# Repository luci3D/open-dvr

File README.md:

# open-dvr

An open recorder for the BAYCKRC / COOAI "MINI DVR", a small analog FPV DVR board (Goke GK7202V300 SoC + Techpoint TP2850 video decoder). It's built on open-source work from the [OpenIPC](https://openipc.org) project.

- Real 50 fps PAL and 59.94 fps NTSC: every video field is recorded, where the stock firmware repeats each picture twice.
- H.264 in MPEG-TS clips, safe against power cuts, with the board's microphone as an in-sync MP3 track.
- Runs from the SD card through the board's own boot hook. Nothing is flashed, and removing the files brings back the stock firmware.

| Folder | What |
|---|---|
| [`dvr-recorder/`](dvr-recorder/) | The recorder (`dvrrec`): specs, wiring, settings, build steps, credits |
| [`dvr-probe/`](dvr-probe/) | The SD card probe script used to work out the hardware |
| [`imu-probe/`](imu-probe/) | IMU test for the next, Rockchip-based generation (see [`ROADMAP.md`](ROADMAP.md)) |

Quick start: download `open-dvr-0.9.zip` from the [Releases](https://github.com/luci3D/open-dvr/releases) page, extract it into the top folder of the board's SD card, and power on. The zip has its own `README.txt` with the button, the LEDs and every `config.txt` setting. The technical details are in [`dvr-recorder/README.md`](dvr-recorder/README.md).

Where the project goes from here: [`ROADMAP.md`](ROADMAP.md). Stage 1, this board, is done; stage 2 is our own hardware on the Rockchip RV1103.

## Licence

GPL-3.0, see [`LICENSE`](LICENSE). Third-party parts keep their own licences; see [Credits and licences](dvr-recorder/README.md#credits-and-licences).

Not affiliated with OpenIPC or with the board's maker.

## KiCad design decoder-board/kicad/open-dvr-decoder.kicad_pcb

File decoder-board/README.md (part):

# Decoder board (phase 1): the DIY kit board

A small board that turns an analog FPV camera signal (CVBS) into MIPI CSI-2 for a Luckfox Pico, and carries the DVR's microphone. Plugged into a Luckfox Pico Pro/Max with the camera ribbon cable and a few wires, it makes a complete DVR module. It is **our first piece of hardware and the DIY kit board** (decided 2026-11-19): video decoder and mic, on a separate board connected by cable. The IMU stays a separate breakout for later ([roadmap phase 4](../ROADMAP.md#phase-4-imu-breakout)).

Status: **schematic v0.1, PCB placed and routed v0.1, 2026-11-19** ([`kicad/`](kicad/), see [Schematic](#schematic) and [PCB](#pcb)). Next: a review in KiCad, then a JLC order.

| Top | Bottom |
|---|---|
|  |  |

KiCad 3D renders of v0.2 with all parts fitted (U1 and MK1 included, though they are soldered at home).

```
FC video line ──(parallel tap)──► J2/J3 ──► input network ──► TP9950 ──MIPI 2 lanes + I2C──► J1 FPC ──► Luckfox camera connector
FC 5 V ──► J2/J3 ──► reverse-polarity FET ──► 5 V ──► 3.3 V LDO, 1.2 V buck, camera 5 V out (J3), 5 V to Luckfox VSYS (J3)
MEMS mic ──► J3 ──(3 short wires)──► Luckfox codec pads 3/4 + GND
```

## Connectors

| Ref | Type | Pins | Goes to |
|---|---|---|---|
| J1 | FPC 0.5 mm 20-pin, **top contact** (05B20U20P, JLC-assembled) | Luckfox camera pinout, pin n = Luckfox pin n | Luckfox camera connector, stock opposite-side cable |
| J2 | SH 1.0 mm 3-pin (JLC-assembled) | 1 Video, 2 5 V in, 3 GND | The FC: camera video line (parallel tap) and 5 V; same harness as the COOAI DVR |
| J3 | One row of 10 holes, 2.54 mm, along the bottom edge (not assembled) | see below | Wires, or a 10-pin header for a breadboard |

J3, labelled on the silkscreen, left to right:

| Pin | Label | Net | Goes to |
|---|---|---|---|
| 1 | VID | Video in | Same as J2 pin 1 |
| 2 | VG | Video ground sense (VID_REF) | The camera's ground at the tap, on its own wire twisted with VID. Optional: R16 ties it to GND (see [Video input network](#video-input-network)) |
| 3 | 5Vin | 5 V in | Same as J2 pin 2 |
| 4 | GND | GND | |
| 5 | CAM | Camera 5 V out, through the polyfuse | A camera on the bench |
| 6 | GND | GND | |
| 7 | VSYS | 5 V out | Luckfox **VSYS (header pin 39)**: one 5 V feed from the FC powers both boards. VSYS is the Luckfox's 5 V system rail; its USB-C input reaches it through a Schottky diode, so USB can stay plugged in |
| 8 | M+ | Mic + | Luckfox codec pad 3 (MIC0+) |
| 9 | M− | Mic − | Luckfox codec pad 4 (MIC0−) |
| 10 | GND | GND | Luckfox header pin 23 (mic ground) |

The schematic first had four separate hole groups (J3–J6). They didn't fit across the board edge, so they became one 10-hole row, which is also easier for a breadboard.

## Chip: TP9950 instead of TP2850

| | TP2850 (COOAI board) | TP9950 |
|---|---|---|
| Datasheet | Not found | Preliminary datasheet, rev A (2018-12-28) |
| Sourcing | No listing found anywhere | Listed in JLCPCB's assembly library (C2852602 and others), so JLC can place it |
| Package | QFN, about 10 pins per side in the photo, so probably QFN40 | EPQFN40, 5 x 5 mm, 0.4 mm pitch, exposed pad 3.7 mm |
| Linux driver | None | Rockchip's open TP9950 driver, the one the roadmap already plans to use |
| Registers | Our probes found the same CVBS tables as the TP9950 driver | |

**Pick: TP9950.** It is the chip the driver is written for, it has a datasheet, and it can be bought assembled. The TP2850 on the COOAI board is still useful as a working reference: same package size and same register tables, so it is most likely the same pinout. That needs a continuity check (see [Checks on the COOAI board](#checks-on-the-cooai-board)).

The datasheet is marked confidential, so it is **not** stored in this repo. Only the facts needed for the design are copied here.

## TP9950 pin map

Pin numbers from the TP9950 datasheet (top view, pin 1 = AVDD33, counter-clockwise). "Our net" is what each pin connects to on this board.

| Pin | Name | Type | Our net / connection |
|---|---|---|---|
| 1 | AVDD33 | Power | `3V3A`: 3.3 V through a ferrite bead, 100 nF + 1 µF at the pin |
| 2 | AVDD12 | Power | `1V2A`: 1.2 V through a ferrite bead, 100 nF + 1 µF at the pin |
| 3, 4 | PTZ1, PTZ2 | Out | Not connected (PTZ data over coax, not used) |
| 5, 6 | DIAG1, DIAG2 | In | Not connected (input fault detection, not used). Check the datasheet's "use as directed" note before layout |
| 7 | VIN1 / VIN1P | Analog in | Video input, AC-coupled 0.1 µF (see input network) |
| 8 | VIN2 / VIN1N | Analog in | Pseudo-differential return: 0.1 µF to the video ground pad (to confirm, see below) |
| 9, 10 | VIN3-4 / VIN2P/N | Analog in | Not connected |
| 11, 28, 40 | DVDD | Power | `1V2D`: 1.2 V core, 100 nF at each pin + 10 µF bulk |
| 12, 13 | VS, HS | Out | Not connected (parallel output not used); test pads optional |
| 14, 27, 35 | VDD_IO | Power | `VIO`: 1.8 V from U4 (the Luckfox camera I/O is 1.8 V); 0 Ω option for 3.3 V, not fitted |
| 15 | RSTB | In, low active | Host reset line from the FPC (pin 16), plus 10 kΩ pull-up to `VIO` and 100 nF to GND (power-on reset if the host leaves it floating) |
| 16 | SCL | In | Host I2C SCL from the FPC (pull-ups on the Luckfox; footprints for our own, not fitted) |
| 17 | SDA | Bidir | Host I2C SDA, same as SCL |
| 18 | IRQ | Out | Test pad (not needed by the driver) |
| 19, 20, 29-34 | VD1_0-7 | I/O | Not connected (parallel BT.656 output, not used) |
| 21 | CKN | Out | MIPI clock − |
| 22 | CKP / CLKO | Out | MIPI clock + |
| 23, 24 | D0N, D0P | Out | MIPI lane 0 −/+ |
| 25, 26 | D1N, D1P | Out | MIPI lane 1 −/+ |
| 36 | XTI | In | 27 MHz crystal, or a 27 MHz clock in (see clock) |
| 37 | XTO | Out | 27 MHz crystal |
| 38 | SAD | In | GND → I2C address `0x44` (VIO → `0x45`). `0x44` is what the COOAI board and our driver tables use |
| 39 | TEST | In | GND (to confirm on the COOAI board) |
| EP | GND | | Ground, with a via array under the pad |

## Power

From the datasheet:

| Rail | Range | Current (typ.) |
|---|---|---|
| AVDD33 | 3.15–3.45 V | 24 mA |
| AVDD12 | 1.1–1.3 V | 60 mA |
| DVDD | 1.1–1.3 V | 84 mA at 720p and below (140 mA at 1080p30) |
| VDD_IO | 3.15–3.45 V or 1.7–2.0 V | 9 mA |

So the chip needs about **35 mA at 3.3 V and 145 mA at 1.2 V**, roughly 0.3 W. The power table in the datasheet also has a limit on the difference between VDD_IO and AVDD that didn't extract cleanly; read it on the PDF before choosing 1.8 V IO.

**Plan:** power the board from its own **5 V pad**, the same one that feeds the camera, instead of the Luckfox connector's 3.3 V. This answers the roadmap's open question: the board doesn't depend on how much the Luckfox's 3.3 V can supply. On the bench, the 5 V comes from the Luckfox VBUS pin; on a quad, from the FC's 5 V pad.

| Rail | Part type | Why |
|---|---|---|
| 3.3 V (`3V3A`, and `VIO` if 3.3 V) | Low-noise LDO, 5 V → 3.3 V, 150–300 mA, SOT-23-5 | Only about 35 mA, so about 0.06 W lost; quiet supply for the analog front end |
| 1.2 V (`1V2A`, `1V2D`) | Small buck, 5 V → 1.2 V, 2.5–5.5 V input (SY8089 / TLV62569 class), 2.2 µH | An LDO from 3.3 V would burn about 0.3 W at 145 mA. Ferrite + caps split it into analog and digital 1.2 V |
| 1.8 V (`VIO`) | Tiny LDO, 3.3 V → 1.8 V | The Luckfox camera I2C and reset are 1.8 V (see below) |
| Camera power out | 5 V pass-through, ferrite + 22 µF, polyfuse | See [Camera input in the roadmap](../ROADMAP.md#camera-input-standard-3-wire-analog-fpv-camera-v-gnd-video) |

Input protection on the 5 V pad: 5 V TVS, bulk 10–22 µF, and reverse-polarity protection. The COOAI board has an SMA-package diode marked `BV` next to its connector, most likely for the same job.

## I/O voltage

**The Luckfox camera I/O is 1.8 V** (Luckfox Pico Pro/Max schematic): the SoC's camera pins are on the `VCCIO7` domain, powered from `VCC_1V8`, and the camera I2C pull-ups (R28, R29, 4.7 kΩ) go to `VCC_1V8`.

So `VIO` = **1.8 V**: U4 (1.8 V LDO) is fitted, and the TP9950's I2C and reset talk to the Luckfox directly, with no level shifter. The 0 Ω option to run `VIO` from 3.3 V stays on the board, not fitted.

Still to read on the datasheet PDF: the power table's limit on the difference between VDD_IO and AVDD, which didn't extract cleanly. The datasheet does list 1.8 V as a supported VDD_IO.

## Clock

- **27 MHz fundamental crystal**, ±50 ppm, CL 20 pF, ESR about 80 Ω (datasheet values). 3225 package.
- Load caps: start at 33 pF each (2 × (20 pF − about 4 pF stray)); copy the COOAI board's values if they can be measured.
- The COOAI board uses a 27 MHz crystal next to its decoder (the can marked `R27.0` in the photo).
- **Optional:** XTI also accepts a 27 MHz clock in. Add a 0 Ω (not fitted) from the FPC's MCLK pin to XTI, in case we ever want to drop the crystal and have the Luckfox drive it. The crystal is the default because it doesn't depend on the host's clock setup.

## Video input network

```
Video pad ──┬── ESD diode (<1 pF) ── GND
            ├── 75 Ω ── JP1 (open by default) ── GND
            └── 0.1 µF ── VIN1P (pin 7)

J3 VG (camera ground sense) ──┬── 0.1 µF (C13) ── VIN1N (pin 8)
                              └── 75 Ω (R16) ── GND
```

- The datasheet asks for the input to be AC-coupled with **0.1 µF**.
- **JP1 is open by default:** on the quad the DVR is a parallel tap, and the FC (or VTX) already terminates the line (see [Requirements](../ROADMAP.md#requirements)). Close it on the bench when the camera is wired straight in.
- **Pseudo-differential input (v0.2):** VIN1N's cap C13 goes to its own net, VID_REF, which leaves the board on J3 VG.
  - **Wiring:** solder a wire from VG to the camera's ground at the same point where VID is tapped, and twist it with the VID wire. That wire carries no power current, so it holds the camera's ground voltage. The chip then measures the video against the camera's ground, and ground noise between the quad and the DVR (ESC and camera currents in the ground wires) cancels.
  - **R16 (75 Ω to GND):** keeps the input working when VG isn't wired, and then it behaves like v0.1. With the wire connected, only a fraction of a milliamp of ground noise flows through R16, which the sense wire swamps.
  - **To compare:** short R16 with solder or a 0 Ω and you're back to the v0.1 behaviour, so the two can be A/B tested on the bench.
  - **Still to confirm:** the datasheet section on the negative input didn't extract cleanly. Check it on the PDF and on the COOAI board.

## Host connector (FPC)

From the Luckfox Pico Pro/Max schematic, connector `H1` (`CAM`), **0.5 mm, 20 pins**:

| Pin | Luckfox net | Our board |
|---|---|---|
| 1 | GND | GND |
| 2 | `MIPI/LVDS_MCLK0` (SoC `VI_CIF_CLKO_M0` / GPIO3_C4, through 22 Ω) | Optional 0 Ω to XTI, not fitted |
| 3 | GND | GND |
| 4 | `MIPI/LVDS_D0_P` | D0P (TP9950 pin 24) |
| 5 | `MIPI/LVDS_D0_N` | D0N (pin 23) |
| 6 | GND | GND |
| 7 | `MIPI/LVDS_CLK_P` | CKP (pin 22) |
| 8 | `MIPI/LVDS_CLK_N` | CKN (pin 21) |
| 9 | GND | GND |
| 10 | `MIPI/LVDS_D1_P` | D1P (pin 26) |
| 11 | `MIPI/LVDS_D1_N` | D1N (pin 25) |
| 12 | GND | GND |
| 13 | `MIPI_I2C_SCL` (4.7 kΩ to 1.8 V on the Luckfox) | SCL (pin 16) |
| 14 | `MIPI_I2C_SDA` (4.7 kΩ to 1.8 V on the Luckfox) | SDA (pin 17) |
| 15 | GND | GND |
| 16 | `MIPI/LVDS_RST` (SoC GPIO3_C5) | RSTB (pin 15) |
| 17, 18 | GND | GND |
| 19, 20 | `VCC_3V3` | Not used for power; optional 0 Ω to our 3.3 V rail, not fitted |

**Cable** (measured on the bench, 2026-11-17, with the cable plugged into the Luckfox and a meter on the 3.3 V header pin):
- The stock Luckfox camera cable (0.5 mm, 20 conductors) has its contacts on **opposite faces** at its two ends.
- At the free end, looking at the contacts with the cable's tip pointing toward you (the cable running away from you to the Luckfox): **pins 19–20 (3.3 V) are on the right**, so pin 1 is on the left.

**J1 is a top-contact connector** (HanElectricity 05B20U20P, LCSC C22435648), changed from the bottom-contact 05A20L20P during layout (2026-11-19):
- **Cable fit:** a top-contact connector takes the cable the way it naturally lies, contacts facing up. The bottom-contact part needed the cable turned over.
- **MIPI polarity:** with a top-contact J1, seen from above with the cable coming in from the top edge, **Luckfox pin 1 lands on the left**, and every MIPI pair's + and − line up with the TP9950's pins. With the bottom-contact part, all three pairs came out reversed.
- **Mapping:** the cable enters opposite the solder leads (drawing and product photo). With the footprint turned 180° so the entry faces the board edge, pad 1 is on the left, so **J1 pad n = Luckfox pin n**.
- **Not double-sided:** some "double-sided contact" parts accept the cable either way up; upside down, that would short the Luckfox's 3.3 V to GND. A single-sided part avoids that.

**Spare cables** must also be **opposite-side** (sometimes sold as "Type B" or "reverse"), 0.5 mm, 20 conductors. A same-side cable mirrors the pin order and won't work with this layout.

Still to check: the Mini B uses the same 20-pin pinout (the SC3336 camera fits both, which suggests yes).

## Microphone

The mic goes on this board because it is the board that sits on the quad next to the video wiring, and it already has clean local supplies. That saves a separate mic board for the DIY kit.

**Requirement** (from the COOAI board, see [bom-prelim.md](../dvr-recorder/docs/bom-prelim.md#microphone)): prop noise next to the motors is very loud; the COOAI mic input clipped up to 38 % of the time in flight. The mic must not overload before the SoC's input does.

**Where the audio goes:** the RV1106/RV1103 has a built-in audio codec. On the Luckfox Pico Pro/Max its pins come out to **test pads**:

| Pad | Net | SoC pin |
|---|---|---|
| P4 | `MIC0_P` | CODEC_MIC0P (34) |
| P5 | `MIC0_N` | CODEC_MIC0N (33) |
| P7 | `MIC1_P` | CODEC_MIC1P (36) |
| P8 | `MIC1_N` | CODEC_MIC1N (35) |
| P6 | `LINEOUT` | CODEC_LINEOUT (29) |
| P9 | `BIAS` (mic bias, from `VCC1V8_MICBIAS`) | CODEC_MICBIAS (32) |

**Where they are on the board** (confirmed by continuity to the SoC pins, 2026-11-17): the row of **four round gold pads** on the top side, next to the RTC battery connector, just above header pins 21–26. Numbered left to right with the camera connector on the left:

| Pad on the board | SoC pin | Net | Schematic pad |
|---|---|---|---|
| 1 | 29 | `LINEOUT` | P6 |
| 2 | 32 | Mic bias (1.8 V) | P9 |
| 3 | 34 | **`MIC0_P`** | P4 |
| 4 | 33 | **`MIC0_N`** | P5 |

MIC1 (P7, P8) isn't on these pads, and we don't need it.

**Wiring:** the camera FPC carries no audio, so the mic connects with **3 short twisted wires**: MIC+ → pad 3, MIC− → pad 4, GND → header pin 23 (the square pad just below; GND in the Pico pinout, check it beeps to GND). Check the Mini B too.

**Software:** the Luckfox wiki says the Pro/Max "does not expose" the audio pins, and its audio tutorial is for the Ultra W only. The stock image probably has the codec turned off, so expect to enable it in the device tree of our build.

**Plan A, analog mic (default):** Infineon IM73A135, 135 dB SPL overload point, IP57, bottom port, differential output.

### Mic limits (IM73A135V01 datasheet, V1.20)

| Item | Value | What it means for us |
|---|---|---|
| **Absolute max supply** | **3.0 V** | Never connect it to 3.3 V, not even on the bench |
| Supply, normal mode | 2.3–3.0 V (typ. 2.75 V) | Full performance: 135 dB SPL overload, 73 dB SNR. **We use 2.8 V** |
| Supply, low-power mode | 1.52–1.8 V | 130 dB overload. The mode is picked by the supply voltage. Nothing between 1.8 and 2.3 V is specified |
| Current | 170 µA typ., 230 µA max (normal mode) | Any small LDO does it |
| Supply ramp-up | reach final value within 5 ms | Fine for an LDO |
| Start-up time | 10–30 ms | The recorder drops the first ~50 ms of audio |
| Output DC level | 1.35 V on each output | Needs coupling caps: the codec inputs sit at their own bias |
| Output impedance | 250 Ω | |
| Output load | ≤ 100 pF per output and across; tested with 25 kΩ | No big filter caps on the outputs |
| Sensitivity | −38 dBV at 94 dB SPL (±1 dB) | 1 kHz |
| Output at 135 dB SPL | about 1.4 V rms differential (about 4 V peak-to-peak) | Probably more than the codec input takes at 0 dB gain (see below) |
| Pins | 1 Output+, 2 VDD, 3 Output−, 4 GND, 5 GND (sound port ring) | Matches the LCSC symbol |

**The Luckfox mic bias (pad 2, 1.8 V) can't power this mic:** 1.8 V is at the very top of low-power mode, and a little above it is unspecified. The 0 Ω option for it is removed; the mic always runs from our own 2.8 V LDO (U5). The ME6211C28 is ±2 %, so at most 2.86 V, under the 3.0 V limit.

**Codec input level, unknown:** the RV1106 codec's mic input full scale and input impedance aren't in anything we have (the datasheet copy at LCSC didn't download). Its analog supply is 1.8 V, so a full-scale input of roughly 1 V rms differential or less is likely. At 120 dB SPL (prop noise) the mic gives about 0.25 V rms, which is fine; near 135 dB it would clip the codec first. So the board has an **attenuator option**: a series resistor on each line (0 Ω fitted) and a resistor across the pair (not fitted). The breadboard test sets the values.

### Mic circuit (for the schematic)

```
3V3 ── U5 ME6211C28 (VIN, EN) ── 2V8_MIC                    1 µF on U5 in, 1 µF on U5 out
2V8_MIC ── MK1 pin 2 (VDD), 100 nF at the pin
MK1 pin 4, pin 5 ── GND (pin 5 is the ring around the sound port)
MK1 pin 1 (Out+) ── C 1 µF ── R13 0 Ω ──┬── MIC_P pad ──► Luckfox pad 3 (MIC0_P)
                                        R15 (not fitted, across the pair)
MK1 pin 3 (Out−) ── C 1 µF ── R14 0 Ω ──┴── MIC_N pad ──► Luckfox pad 4 (MIC0_N)
GND pad ──► Luckfox header pin 23
```

- **Coupling caps:** 1 µF X5R/X7R. The DC across them is small (1.35 V on the mic side, the codec's bias on the other), so microphonic pickup from vibration should be low; listen for it in the strapped-down motor test.
- **Footprint:** the LCSC footprint (named after the IM69D130, same package) matches the IM73A135 drawing: pad positions, pin 1 and 0.75 × 0.45 mm pads. Its sound hole was 0.7 mm; it's changed to the datasheet's **0.8 mm** in `kicad/lib/lcsc.pretty` (redo this if the footprint is downloaded again).
- **Pads:** MIC+, MIC−, GND at the board edge, next to the camera pads but away from the 1.2 V buck. Twist the three wires to the Luckfox.
- **Port hole:** cover it with acoustic mesh or foam against wind and prop wash.

### Bench test of the mic

No separate mic breakout: the first decoder boards are the test boards. With a 10-pin header in J3 the board plugs into a breadboard.

1. With 5 V on J3 pin 2, measure VDD at the mic's 100 nF cap (C14): 2.74–2.86 V.
2. Wire J3 pins 8, 9 and 10 (M+, M−, GND) to the Luckfox codec pads 3 and 4 and header pin 23, enable the codec in the Luckfox device tree and record with `arecord`.
3. Levels: speech, then a speaker close to the mic, then motors on a strapped-down quad. If it clips at the codec's lowest gain, fit R15 (and resistors in place of R13/R14) to attenuate, and note the values for the next revision.
4. Listen for vibration noise and for whine from the motors' ESCs on the wires.

**Plan B, digital I2S mic:** only needed if a board doesn't bring out the codec mic pins (the Pro/Max does). The RV1106 has an I2S0 port (`I2S0_SCLK`, `I2S0_LRCK`, `I2S0_SDI0` on GPIO2_A0, A1 and A5 in the Ultra W schematic). An I2S MEMS mic needs 3 wires plus power, and its audio arrives already digital, so no analog noise pickup on the wires. The catch is overload: common I2S mics are around 120 dB SPL, below the IM73A135. Keep a footprint for one only if plan A is ruled out.

## Schematic

[`kicad/open-dvr-decoder.kicad_sch`](kicad/open-dvr-decoder.kicad_sch) (KiCad 10, project `open-dvr-decoder`). Version 0.1 was generated by [`kicad/tools/gen_schematic.py`](kicad/tools/gen_schematic.py), whose netlist table is the design in text form. Nets connect through labels; each block on the sheet has a title. From now on, edit the schematic in KiCad and don't rerun the generator (it would overwrite the edits).

Checked with `kicad-cli` (2026-11-19):
- **ERC:** no errors. 81 warnings, all "unspecified pin connected to passive pin": the LCSC symbols mark every pin as unspecified. Harmless.
- **Netlist:** the exported netlist matches the generator's table exactly: 39 nets, 190 connected pins, and the 20 unused TP9950 pins marked no-connect.
- **Part libraries:** `kicad/sym-lib-table` and `kicad/fp-lib-table` add the `lcsc` library from `kicad/lib/`. The FPC footprint's two mounting tabs were numbered `0`; they're now 21 and 22 to match its symbol.

Not fitted (DNP): R10 (VIO from 3.3 V), R11 (MCLK to XTI), R12 (Luckfox 3.3 V to our 3.3 V), R15 (mic attenuator). The I2C pull-ups R7/R8 were removed during routing; the Luckfox has them.

## PCB

[`kicad/open-dvr-decoder.kicad_pcb`](kicad/open-dvr-decoder.kicad_pcb), v0.1 (2026-11-19). Placement made by [`kicad/tools/gen_pcb.py`](kicad/tools/gen_pcb.py) from the schematic's netlist, routing by [`kicad/tools/route/`](kicad/tools/route/). From now on, edit the board in KiCad; rerunning either would overwrite it.

**Board:**
- 28 × 38 mm, 4 layers, 1.6 mm (JLC standard): F.Cu signals, **In1 GND plane**, **In2 GND plane**, B.Cu signals. Two M2 holes in the top corners.
- J1 on the top edge (the cable enters from the edge); the TP9950 right below it with its MIPI side facing J1; crystal to its left; decoupling around it.
- Left: J2 and the video input (ESD diode, 75 Ω + JP1), and the 5 V input protection (Q1, D2, C28).
- Right: the 1.2 V buck and its inductor, away from the video input and the mic. Middle: the 3.3 V and 1.8 V LDOs.
- Bottom right: the mic with its LDO and coupling caps, as far from the buck as the board allows.
- Bottom edge: J3, one row of 10 labelled holes. The project name and version are on the back silkscreen.

**Rules and net classes** (in the project file):

| Class | Nets | Track | Clearance | Diff pair |
|---|---|---|---|---|
| Default | everything else | 0.15 mm | 0.15 mm | |
| Power | VIN_RAW, 5V, CAM_5V*, SW_1V2, 1V2, 3V3 | 0.4 mm | 0.2 mm | |
| MIPI | MIPI_* | 0.2 mm | 0.15 mm | 0.2 mm wide, 0.2 mm gap |
| Analog | VIDEO_IN, VIN1P/N, TERM, MIC_* | 0.2 mm | 0.2 mm | |

Board minimums (JLC 4-layer): 0.1 mm track and clearance, vias 0.5/0.3 mm, 0.3 mm copper to edge. The MIPI pair size gives about 100 Ω by hand calculation over JLC's 0.21 mm 7628 prepreg; check it in JLC's impedance calculator before ordering. At these data rates and lengths (under 10 mm) it isn't critical.

**Footprint fixes made during placement:**
- **Courtyards:** every footprint downloaded from EasyEDA had a courtyard covering only the body, so pads could overlap without DRC noticing. All 12 now cover body + pads + 0.25 mm.
- **Mic sound hole:** now a plated 0.8 mm hole tied to GND inside the mic's ground ring (it was a plated hole with no copper ring).

### Routing (v0.1, 2026-11-19)

**Fully routed:** 0 unconnected, **DRC 0 errors** (6 cosmetic silkscreen warnings: Y1's outline touching C2's, pin-1 dots on their own pads), schematic parity clean. 295 mm of track on F.Cu, 95 mm on B.Cu, 93 vias (53 of them GND vias into the inner planes).

**Hand-routed** (exact coordinates in `HAND_TRACKS` in [`tools/route/route.py`](kicad/tools/route/route.py)):
- **MIPI:** lane 0 and the clock straight up to J1 on F.Cu, 0.2 mm tracks at the TP9950's 0.4 mm pitch; skew within each pair under 0.05 mm. **Lane 1 crosses under them on B.Cu** with a via pair at each end (In2 is GND, so it keeps a reference plane). The crossing is unavoidable: the TP9950's pin order is clock, lane 0, lane 1, the Luckfox connector's lane 0, clock, lane 1, and the chip can't swap lanes or invert polarity.
- **I2C and reset:** the TP9950's right side has SDA, SCL, RSTB top to bottom, J1 wants SCL, SDA, RSTB left to right, so **SDA hops to B.Cu** to cross SCL.
- **Crystal:** XTI over Y1 to its far pad (with C1 and the R11 option), XTO straight in.
- **Video pair:** pins 7/8 to C12/C13 at 0.4 mm pitch with the exact 0.2 mm Analog clearance.
- **Supply escapes:** VIO/DVDD from pins 27/28 between the lane 1 vias and pin 29, and the short runs from pins 11, 14 and 35 to their caps.
- **Thermal vias:** four in the TP9950's exposed pad.

**Everything else** was routed by a small grid router written for this board ([`tools/route/`](kicad/tools/route/)): A* on a 0.05 mm grid over F.Cu and B.Cu with vias, keeping the net-class clearances (with a margin for shapes off the grid). GND pads get a short trace to a via into the inner planes. KiCad's DRC is the judge of the result. To re-route from scratch (this replaces every track and via, including hand edits made in KiCad; needs numpy):

```powershell
powershell -ExecutionPolicy Bypass -File decoder-board\kicad\tools\route\route_board.ps1
```

**Changes made for routing:**
- **R7, R8 removed** (the not-fitted I2C pull-ups): the Luckfox already has 4.7 kΩ pull-ups to 1.8 V, and the two parts blocked the I2C escape.
- **Placement:** C6/C9 moved left of the TP9950's corner (room for the lane 1 vias); Y1 rotated 270° so XTI and XTO don't cross, with C1, C2, C7 and R11 moved to match; C22/C23 and R13/R14 turned 180° so the mic chain runs straight to J3; R15 moved.
- **Net classes:** DVDD left the Power class (a 0.4 mm track can't leave a 0.4 mm-pitch QFN pin); the MIPI pair gap is 0.2 mm (the TP9950's pitch).

**Worth a look in KiCad before ordering:** the router's tracks are correct but not pretty; some take detours that a person would shorten (VIDEO_IN is 23 mm from J2 to C12, 3V3 and 5V wander). Nothing in the high-speed or analog paths depends on that, but tidying them is an easy first KiCad session.

**Regulator noise check (2026-11-19, after the hand tidy):** U3 (TLV62569, 1.5 MHz buck with L1) is the only switching regulator; U2, U4 and U5 are LDOs. Measured edge to edge from the switch node copper (U3 pin 3, L1 pin 1): video (VIDEO_IN, VIN1P/N) 8 mm or more, MIPI 9 mm, crystal 12 mm, mic 11 mm, I2C 6.7 mm, RSTB 4.4 mm (a driven, slow line), and the buck's own FB node 2.8 mm (short, keep it that way). The one weak spot was the 3V3 run from C20 up the right edge to R12 (not fitted, FPC 3.3 V option): a 17 mm stub passing 3 mm from L1. It now runs on B.Cu, shielded from the switch node by the two GND planes. The 5V net is long (about 47 mm) because it fans out from Q1/F1 at the bottom left to J3, U2 and U3, but it carries well under 1 A (about 11 mV drop) and the buck's input loop (C25 to U3) is local.

**Signal review (2026-11-21):**

What the review checked:
- **Crosstalk:** checked on both outer layers. Apart from the pairs themselves, the closest signal-to-signal run is RSTB beside SCL (4.1 mm, 0.15 mm gap).
- **Ground planes:** both planes are one piece, with no islands.
- **MIPI pairs:** matched within 0.05 mm, and about 105 Ω differential on the JLC04161H-7628 stackup.

Fixes made:
- **Thermal gap:** reduced from 0.5 to 0.3 mm. At 0.5 mm, J3's pin cut-outs merged into a 17 mm slot in both planes.
- **GND vias:** four added beside MIPI lane 1's layer changes, so its return current can hop between In1 and In2 within about 1 mm.

### v0.2 changes (2026-11-21)

Applied from the signal review:
- **Video reference:** J3 gains a VG pin (video ground sense) next to VID, and C13 now references VIN1N to it. R16 (75 Ω, the same part as R3) ties VG to GND near the pin. To make room, J3's pins 2 to 7 moved up by one, and the spare GND that was next to VSYS is gone.
- **U2 and U4 rotated:** U2 by 90°, U4 by 180°, with C15 and C16 moved 0.2 mm out for U2's courtyard. The 5V, 3V3 and 1V8 runs got shorter:

  | Net | v0.1 | v0.2 |
  |---|---|---|
  | 5V | 47 mm, 9 vias | 40 mm, 5 vias |
  | 3V3 | 51 mm | 41 mm |
  | 1V8 | 13 mm | 12 mm |

- **Mic pair:** MIC_OUTP and MIC_OUTN are hand-routed as a pair at 0.45 mm pitch for 4.9 mm, from MK1 to C22 and C23. 2V8_MIC now enters MK1 from the right to make room. The short MIC_P/MIC_N run to J3 is left to the router.
- **RSTB:** its diagonal starts as late as C8's pad allows. That gives +0.05 mm at the pins and the full diagonal 0.26 mm from SCL, and cuts the coupling by about 26%. The 0.3 mm asked for doesn't fit between C8 and the 0.4 mm pin pitch.
- **Switch-node keep-out:** the router keeps every net that isn't part of the buck at least 4 mm from the switch node on F.Cu. 3V3 is now 3.9 mm away at its closest (it was 2.3 mm after the re-route without the keep-out), and the R12 branch runs on B.Cu.

**Re-routed:** 5V, 3V3, 1V8, VIO, VIN_RAW, CAM_5V, 2V8_MIC, the mic nets, RSTB and VID_REF. Every other track, including the hand tidy, is unchanged.

**Result:** DRC 0 errors, 0 unconnected, parity clean, and the same 6 silkscreen warnings. Each GND plane is still one piece. VID_REF (20 mm, 3 vias) doesn't run beside VIDEO_IN. That's fine: the sense wire is what rejects the ground noise, and over a solid plane the on-board route adds almost nothing.

**Tools for this:**
- `tools/route/update_board.py` brings the routed board in line with the schematic: new parts, net changes, PLACE moves and J3 labels.
- `route.py --reroute NETS` keeps every existing track and routes only those nets.
- `tools/route/reroute.ps1` runs both, then DRC:

```powershell
powershell -ExecutionPolicy Bypass -File decoder-board\kicad\tools\route\reroute.ps1 -Nets "/5V,/3V3"
```

### Look and finish (2026-11-21)

- **Colours:** black solder mask with white silkscreen. Pick the same at JLC when ordering. The board stackup is set to JLC04161H-7628 with those colours ([`tools/stackup.py`](kicad/tools/stackup.py)), so KiCad's 3D view shows the real look.
- **Back silkscreen:** the luci3D logo (12 mm tall) and "luci3d HARDWARE", under "open-dvr decoder v0.2".
  - The logo is one board-only footprint, LOGO1, so you can drag it around in KiCad. It also stays out of the schematic, the BOM and the placement file.
  - It is made from [`art/luci3d-logo.png`](kicad/art/luci3d-logo.png): [`tools/logo/vectorize.py`](kicad/tools/logo/vectorize.py) traces the white strokes and thickens any stroke under 0.16 mm (JLC's silkscreen minimum is 0.15 mm). [`tools/logo/place_logo.py`](kicad/tools/logo/place_logo.py) then places it and saves a copy to `lib/open-dvr.pretty` for other boards.
  - The logo crosses a few vias. They're tented, so the silkscreen prints over them, apart from possible small marks at the via holes.
- **J3:** no 3D pin-header model. Wires are soldered straight into the holes.
- **Silkscreen text:** 0.8 mm tall (J3 labels 0.7 mm to fit the 2.54 mm pitch) with 0.15 mm strokes, JLC's minimum line width. `JLCJLCJLCJLC` on the back marks where JLC prints its order number.

### Ordering

The JLCPCB files (Gerbers, BOM, placement) and the order settings are in [`jlc/`](jlc/README.md). Regenerate them with `tools/jlc_export.py` after any board change.

## Layout

- **4 layers** (JLC 4-layer is cheap; the integrated board will be 4 layers anyway): signals / GND / power / signals.
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
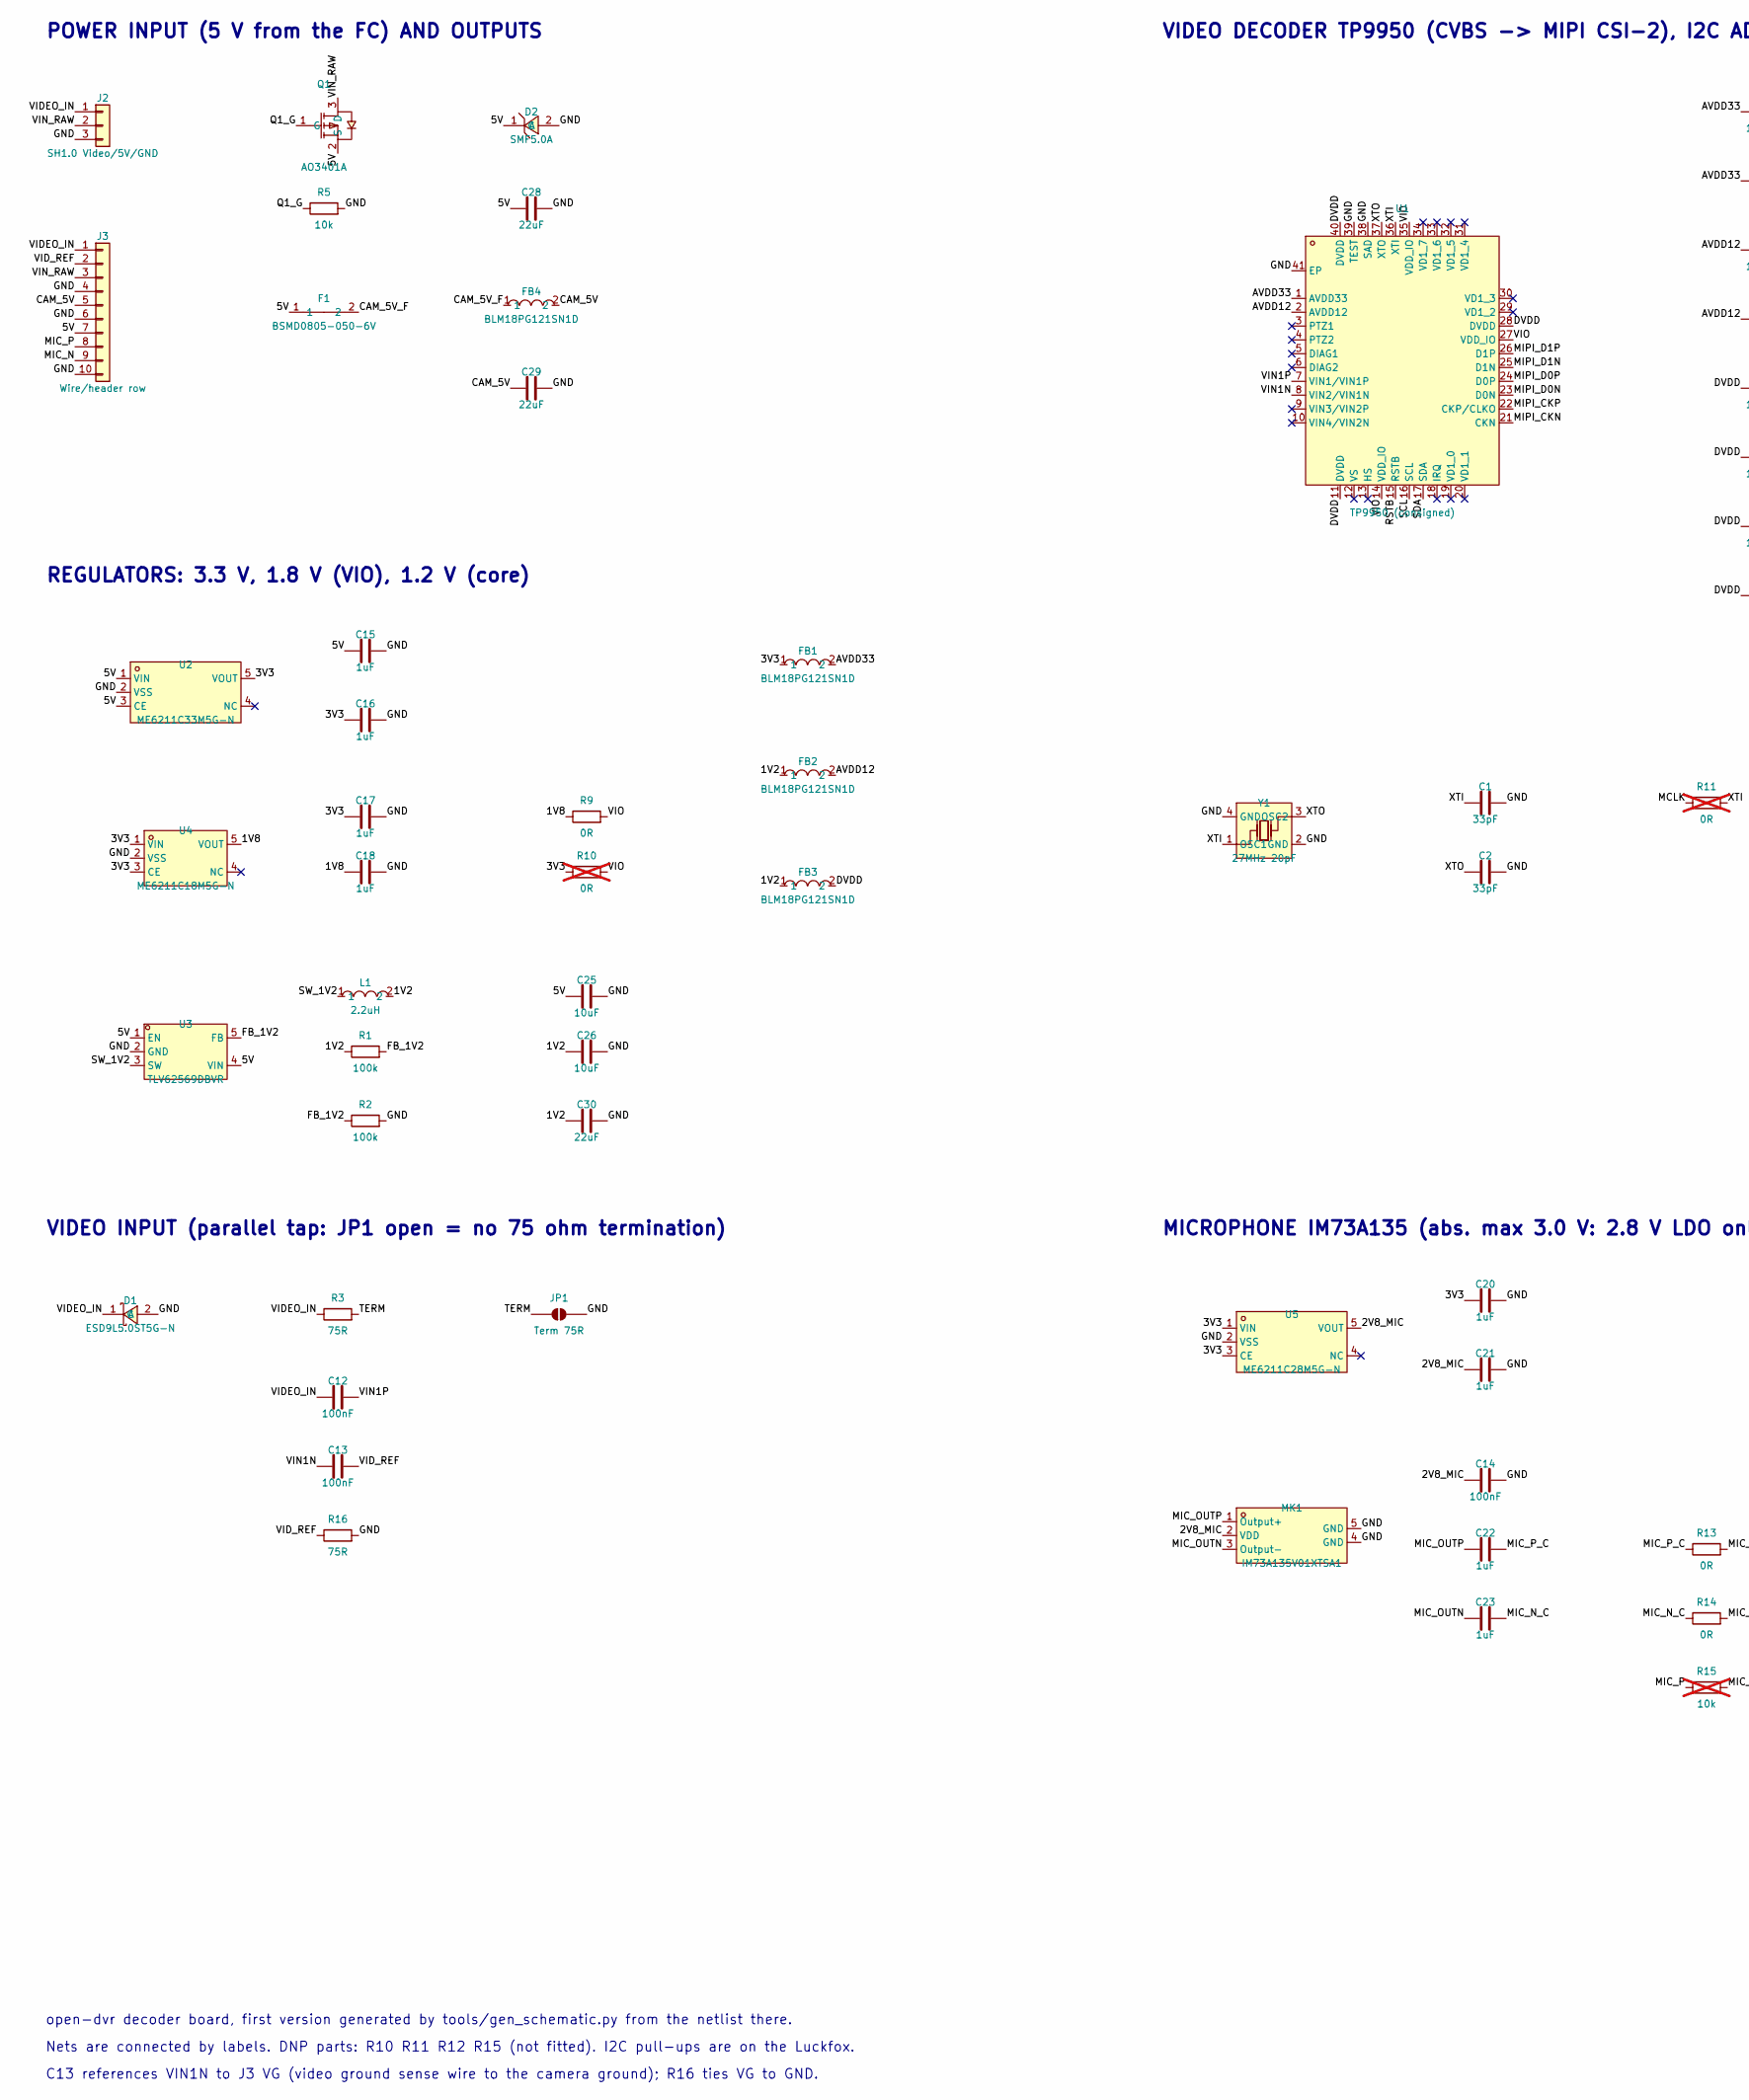
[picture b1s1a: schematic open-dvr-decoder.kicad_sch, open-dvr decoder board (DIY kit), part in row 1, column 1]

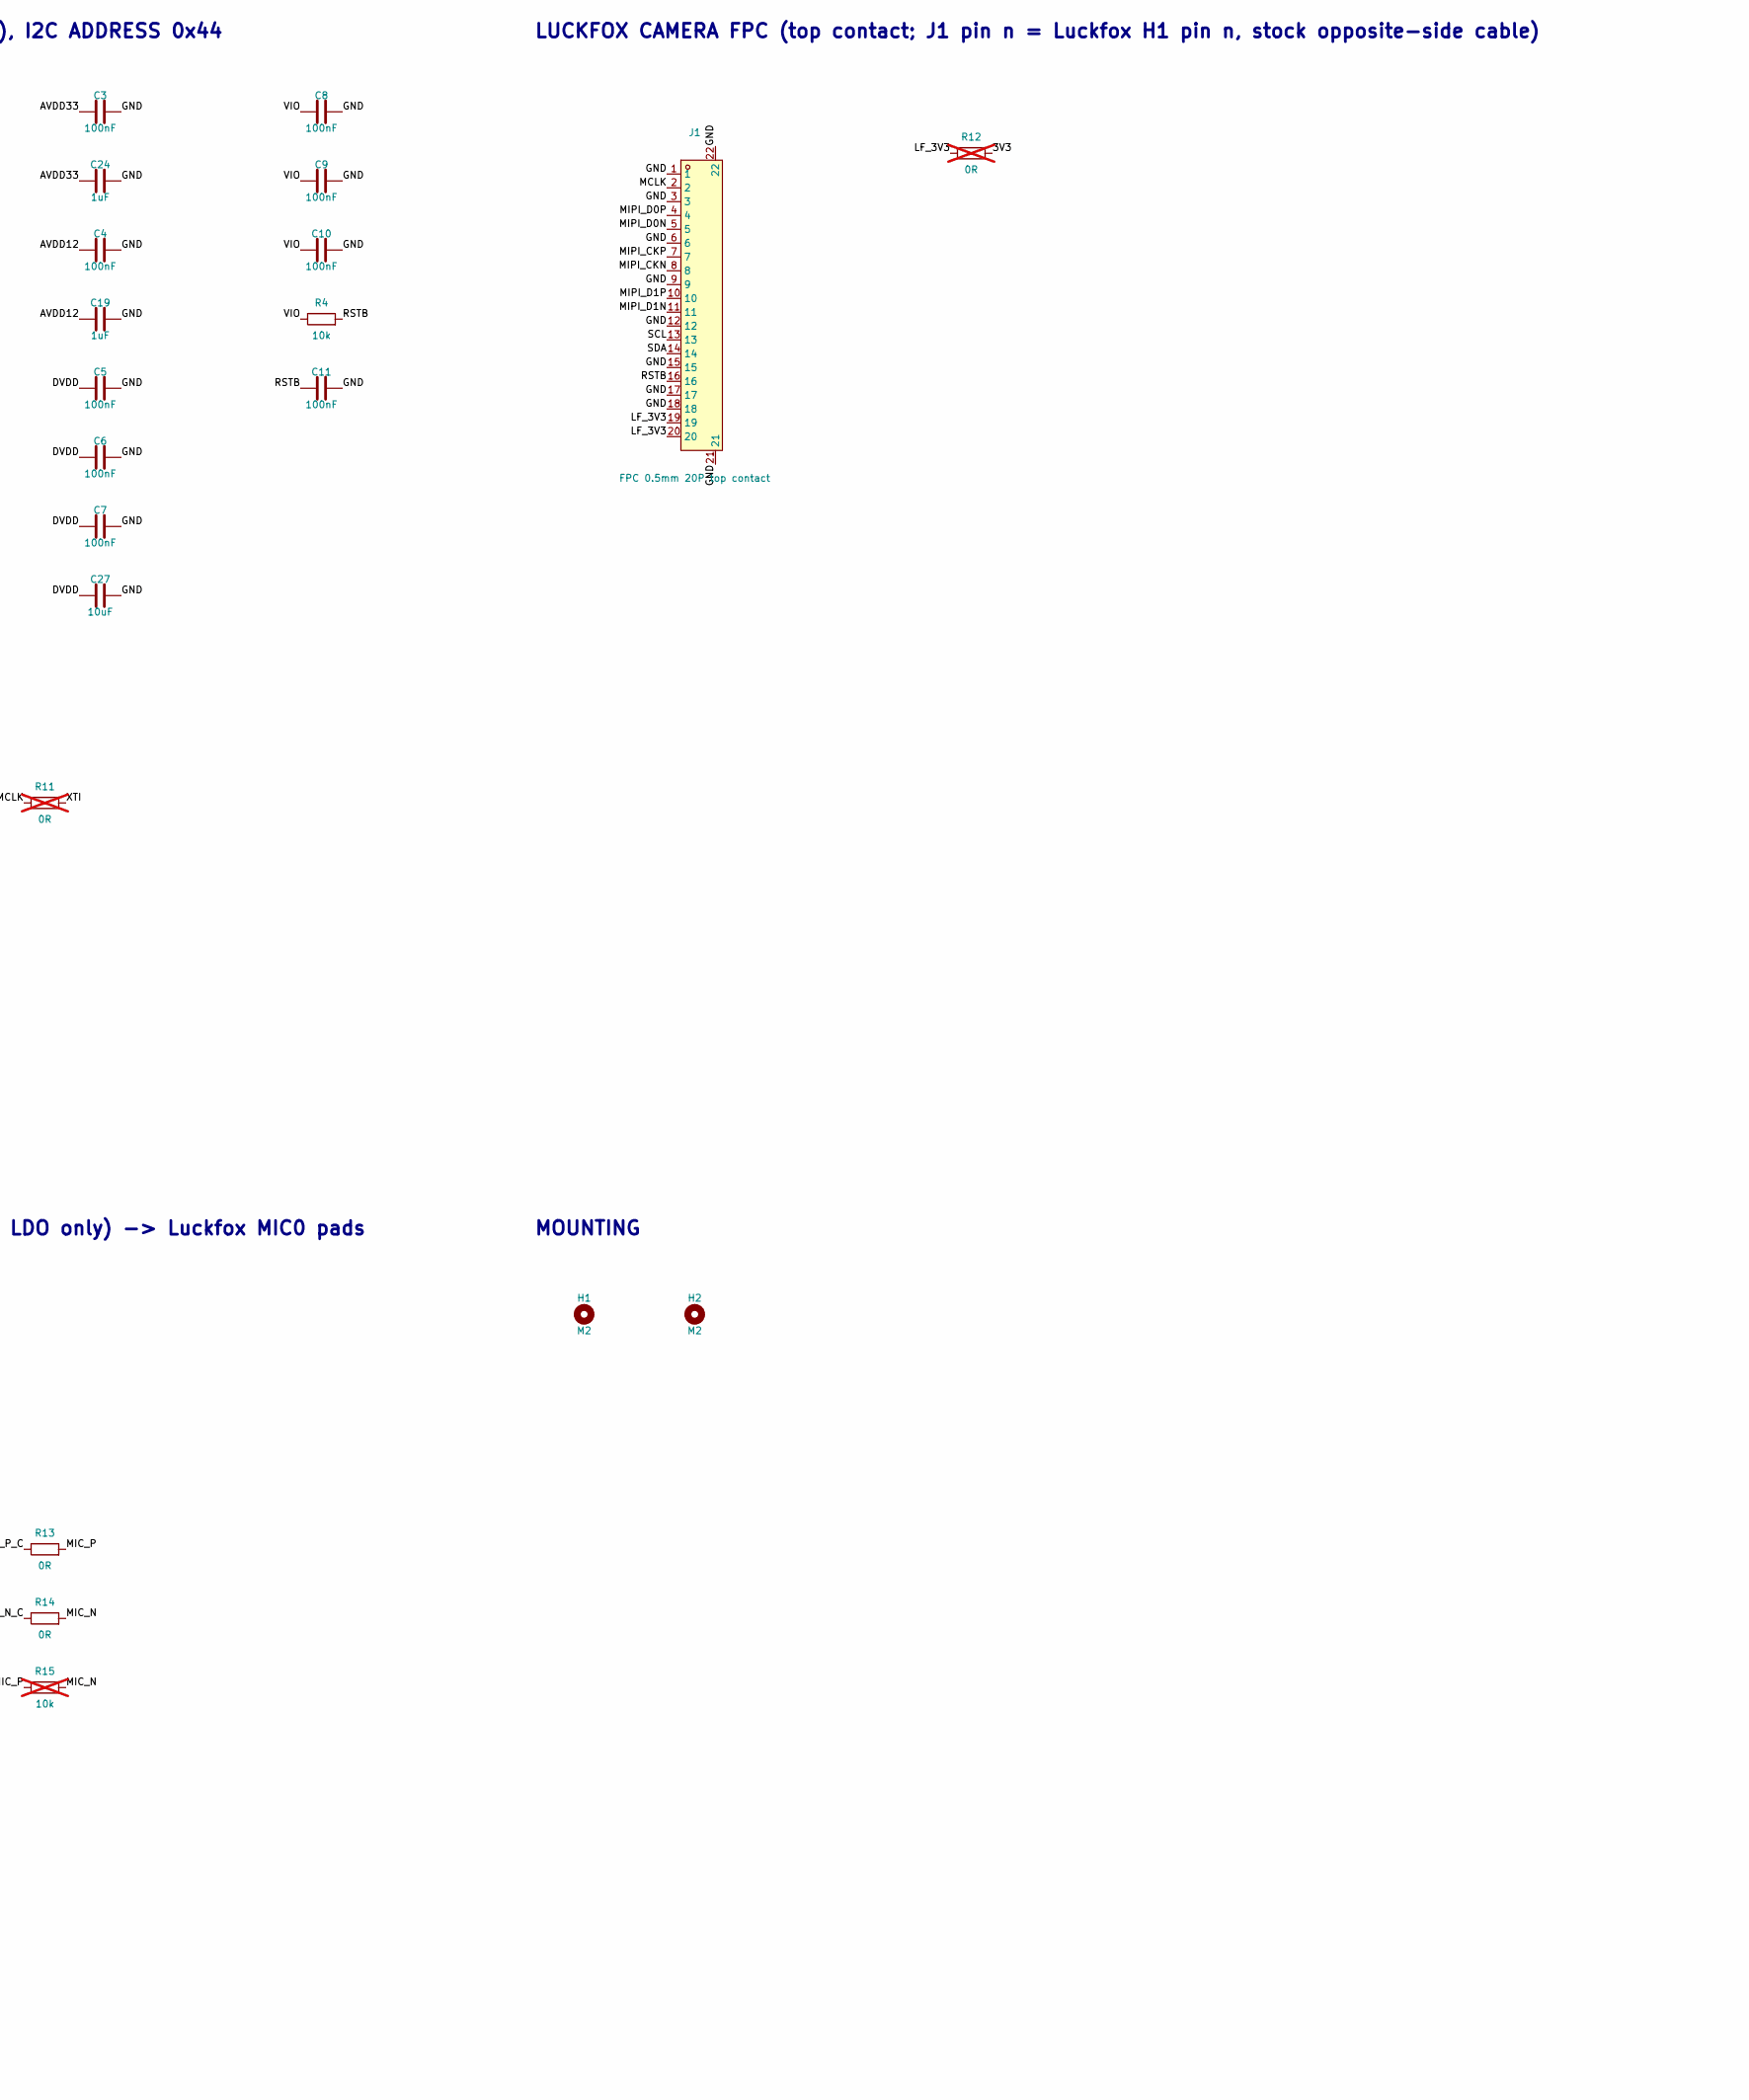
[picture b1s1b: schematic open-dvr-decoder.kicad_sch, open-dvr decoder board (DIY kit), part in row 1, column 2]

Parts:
C1, C2: 33pF; C_0402_1005Metric; LCSC C1562
C3, C4, C5, C6, C7, C8, C9, C10, C11, C12, C13, C14: 100nF; C_0402_1005Metric; LCSC C1525
C15, C16, C17, C18, C19, C20, C21, C22, C23, C24: 1uF; C_0402_1005Metric; LCSC C52923
C25, C26, C27: 10uF; C_0603_1608Metric; LCSC C19702
C28, C29, C30: 22uF; C_0805_2012Metric; LCSC C45783
D1: ESD9L5.0ST5G-N; X1-DFN1006-2_L1.0-W0.6-RD; LCSC C316041
D2: SMF5.0A; SOD-123FL_L2.7-W1.8-LS3.8-RD; LCSC C193402
F1: BSMD0805-050-6V; F0805; LCSC C883108
FB1, FB2, FB3, FB4: BLM18PG121SN1D; L0603; LCSC C14709
H1, H2: M2; MountingHole_2.2mm_M2
J1: FPC 0.5mm 20P top contact; FPC-SMD_20P-P0.50_0.5K-AS-20PWB; LCSC C22435648
J2: SH1.0 Video/5V/GND; JST_SH_SM03B-SRSS-TB_1x03-1MP_P1.00mm_Horizontal; LCSC C3029342
J3: Wire/header row; PinHeader_1x10_P2.54mm_Vertical
JP1: Term 75R; SolderJumper-2_P1.3mm_Open_RoundedPad1.0x1.5mm
L1: 2.2uH; IND-SMD_L2.0-W1.6; LCSC C354533
MK1: IM73A135V01XTSA1; MIC-SMD_5P-L4.0-W3.0-P0.70-TR_IM69D130V01; LCSC C3171831
Q1: AO3401A; SOT-23_L2.9-W1.3-P1.90-LS2.4-BR; LCSC C15127
R1, R2: 100k; R_0402_1005Metric; LCSC C25741
R3, R16: 75R; R_0402_1005Metric; LCSC C25133
R4, R5: 10k; R_0402_1005Metric; LCSC C25744
R9, R13, R14: 0R; R_0402_1005Metric; LCSC C17168
R10, R11, R12: 0R; R_0402_1005Metric; LCSC C17168; not fitted
R15: 10k; R_0402_1005Metric; LCSC C25744; not fitted
U1: TP9950 (consigned); QFN-40_L5.0-W5.0-P0.40-BL-EP3.7; LCSC C2852602
U2: ME6211C33M5G-N; SOT-23-5_L3.0-W1.7-P0.95-LS2.8-BL; LCSC C82942
U3: TLV62569DBVR; SOT-23-5_L3.0-W1.7-P0.95-LS2.8-BR; LCSC C141836
U4: ME6211C18M5G-N; SOT-23-5_L3.0-W1.7-P0.95-LS2.8-BR; LCSC C236671
U5: ME6211C28M5G-N; SOT-23-5_L3.0-W1.7-P0.95-LS2.8-BR; LCSC C53099
Y1: 27MHz 20pF; CRYSTAL-SMD_4P-L3.2-W2.5-BL-1; LCSC C9008

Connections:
/1V2: C26.1, C30.1, FB2.1, FB3.1, L1.2, R1.1
/1V8: C18.1, R9.1, U4.5 (VOUT)
/2V8_MIC: C14.1, C21.1, MK1.2 (VDD), U5.5 (VOUT)
/3V3: C16.1, C17.1, C20.1, FB1.1, R10.1, R12.2, U2.5 (VOUT), U4.1 (VIN), U4.3 (CE), U5.1 (VIN), U5.3 (CE)
/5V: C15.1, C25.1, C28.1, D2.1 (C), F1.1, J3.7, Q1.2 (S), U2.1 (VIN), U2.3 (CE), U3.1 (EN), U3.4 (VIN)
/AVDD12: C4.1, C19.1, FB2.2, U1.2 (AVDD12)
/AVDD33: C3.1, C24.1, FB1.2, U1.1 (AVDD33)
/CAM_5V: C29.1, FB4.2, J3.5
/CAM_5V_F: F1.2, FB4.1
/DVDD: C5.1, C6.1, C7.1, C27.1, FB3.2, U1.11 (DVDD), U1.28 (DVDD), U1.40 (DVDD)
/FB_1V2: R1.2, R2.1, U3.5 (FB)
/GND: C1.2, C2.2, C3.2, C4.2, C5.2, C6.2, C7.2, C8.2, C9.2, C10.2, C11.2, C14.2, C15.2, C16.2, C17.2, C18.2, C19.2, C20.2, C21.2, C24.2, C25.2, C26.2, C27.2, C28.2, C29.2, C30.2, D1.2 (A), D2.2 (A), J1.1, J1.3, J1.6, J1.9, J1.12, J1.15, J1.17, J1.18, J1.21, J1.22, J2.3, J3.4, J3.6, J3.10, JP1.2 (B), MK1.4 (GND), MK1.5 (GND), R2.2, R5.2, R16.2, U1.38 (SAD), U1.39 (TEST), U1.41 (EP), U2.2 (VSS), U3.2 (GND), U4.2 (VSS), U5.2 (VSS), Y1.2 (GND), Y1.4 (GND)
/LF_3V3: J1.19, J1.20, R12.1
/MCLK: J1.2, R11.1
/MIC_N: J3.9, R14.2, R15.2
/MIC_N_C: C23.2, R14.1
/MIC_OUTN: C23.1, MK1.3 (Output-)
/MIC_OUTP: C22.1, MK1.1 (Output+)
/MIC_P: J3.8, R13.2, R15.1
/MIC_P_C: C22.2, R13.1
/MIPI_CKN: J1.8, U1.21 (CKN)
/MIPI_CKP: J1.7, U1.22 (CKP/CLKO)
/MIPI_D0N: J1.5, U1.23 (D0N)
/MIPI_D0P: J1.4, U1.24 (D0P)
/MIPI_D1N: J1.11, U1.25 (D1N)
/MIPI_D1P: J1.10, U1.26 (D1P)
/Q1_G: Q1.1 (G), R5.1
/RSTB: C11.1, J1.16, R4.2, U1.15 (RSTB)
/SCL: J1.13, U1.16 (SCL)
/SDA: J1.14, U1.17 (SDA)
/SW_1V2: L1.1, U3.3 (SW)
/TERM: JP1.1 (A), R3.2
/VIDEO_IN: C12.1, D1.1 (C), J2.1, J3.1, R3.1
/VID_REF: C13.2, J3.2, R16.1
/VIN1N: C13.1, U1.8 (VIN2/VIN1N)
/VIN1P: C12.2, U1.7 (VIN1/VIN1P)
/VIN_RAW: J2.2, J3.3, Q1.3 (D)
/VIO: C8.1, C9.1, C10.1, R4.1, R9.2, R10.2, U1.14 (VDD_IO), U1.27 (VDD_IO), U1.35 (VDD_IO)
/XTI: C1.1, R11.2, U1.36 (XTI), Y1.1 (OSC1)
/XTO: C2.1, U1.37 (XTO), Y1.3 (OSC2)

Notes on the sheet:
POWER INPUT (5 V from the FC) AND OUTPUTS
REGULATORS: 3.3 V, 1.8 V (VIO), 1.2 V (core)
VIDEO DECODER TP9950 (CVBS -> MIPI CSI-2), I2C ADDRESS 0x44
VIDEO INPUT (parallel tap: JP1 open = no 75 ohm termination)
LUCKFOX CAMERA FPC (top contact; J1 pin n = Luckfox H1 pin n, stock opposite-side cable)
MICROPHONE IM73A135 (abs. max 3.0 V: 2.8 V LDO only) -> Luckfox MIC0 pads
MOUNTING
open-dvr decoder board, first version generated by tools/gen_schematic.py from the netlist there.
Nets are connected by labels. DNP parts: R10 R11 R12 R15 (not fitted). I2C pull-ups are on the Luckfox.
C13 references VIN1N to J3 VG (video ground sense wire to the camera ground); R16 ties VG to GND.

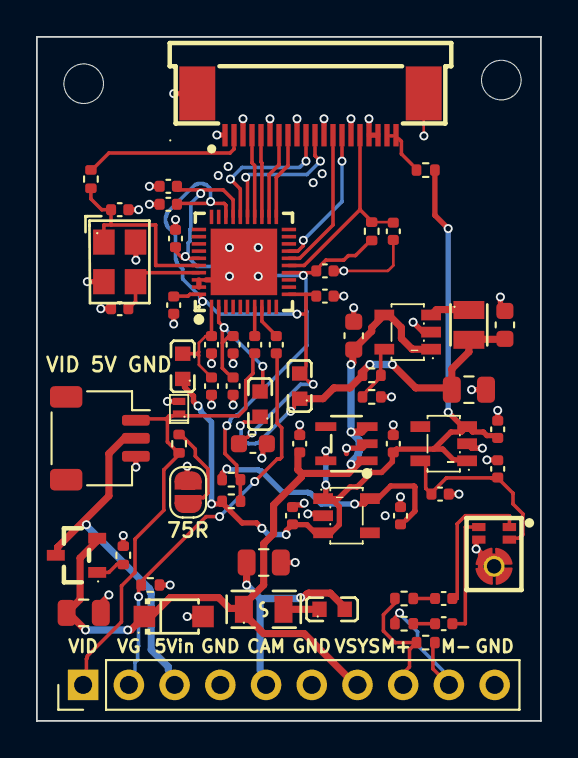
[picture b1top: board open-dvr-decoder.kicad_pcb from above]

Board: 4 copper layers, 28.0 x 38.0 mm, 66 parts (1 on the bottom side), 40 nets.

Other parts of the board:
LOGO1: luci3d_logo

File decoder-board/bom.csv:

Ref,Qty,Description,Package,LCSC,MPN,JLC type,Unit USD,Fitted,Note
U1,1,Video decoder CVBS/AHD to MIPI CSI-2,QFN-40 5x5 EP3.7,C2852602,TP9950,consigned,2.00,yes,Est. price; 0 stock at JLC: buy elsewhere and ship to JLC
Y1,1,Crystal 27 MHz 20 pF +-20 ppm 50 ohm,SMD3225-4P,C9008,X322527MSB4SI,extended,0.1093,yes,
C1-C2,2,Crystal load cap 33 pF C0G,0402,C1562,0402CG330J500NT,basic,0.0024,yes,Tune after first boards
U2,1,LDO 3.3 V 500 mA low noise (AVDD33 + VIO),SOT-23-5,C82942,ME6211C33M5G-N,extended,0.0624,yes,50 uVrms
U3,1,Buck 2 A 1.5 MHz adjustable (1.2 V),SOT-23-5,C141836,TLV62569DBVR,extended,0.0675,yes,2.5-5.5 V in
L1,1,Inductor 2.2 uH 1.1 A shielded,0806 (2016),C354533,CKCS201610-2.2uH/M,extended,0.041,yes,For U3
R1-R2,2,Buck feedback divider 100 k 1%,0402,C25741,0402WGF1003TCE,basic,0.0009,yes,0.6 V x (1 + 100k/100k) = 1.2 V
U4,1,LDO 1.8 V (VIO),SOT-23-5,C236671,ME6211C18M5G-N,extended,0.0658,yes,Luckfox camera I/O is 1.8 V
U5,1,LDO 2.8 V for the mic,SOT-23-5,C53099,ME6211C28M5G-N,extended,0.0653,yes,Mic abs max is 3.0 V: never feed it 3.3 V
FB1-FB4,4,Ferrite bead 120 ohm @ 100 MHz 2 A,0603,C14709,BLM18PG121SN1D,basic,0.014,yes,AVDD33 / AVDD12 / DVDD / camera 5 V
D1,1,Video input ESD 0.6 pF,DFN1006-2,C316041,ESD9L5.0ST5G-N,extended,0.0257,yes,
D2,1,TVS 5 V on the 5 V input,SOD-123FL,C193402,SMF5.0A,extended,0.0284,yes,
Q1,1,P-MOSFET reverse-polarity protection,SOT-23,C15127,AO3401A,basic,0.0814,yes,
F1,1,Polyfuse 500 mA hold 6 V (camera 5 V out),0805,C883108,BSMD0805-050-6V,extended,0.0496,yes,
"R3,R16",2,75 ohm 1% (video termination; VG tie to GND),0402,C25133,0402WGF750JTCE,extended,0.0012,yes,R3 behind JP1 (open by default); R16 ties J3 VG to GND
JP1,1,Termination solder jumper,PCB,,,,0,yes,Open by default
J3,1,Row of 10 x 2.54 mm through-holes,PCB,,,,0,no,Wires or a 10-pin header soldered by the user
H1-H2,2,M2 mounting holes,PCB,,,,0,yes,
MK1,1,MEMS mic analog differential 135 dB SPL,LLGA-5 4x3,C3171831,IM73A135V01XTSA1,extended,3.3492,yes,Bottom port: hole in PCB
J1,1,FPC 0.5 mm 20 P top contact slide lock,SMD P=0.5mm,C22435648,05B20U20P,extended,0.071,yes,20 pins confirmed (Luckfox Pro/Max H1); Luckfox pin 1 lands on the right seen from above with the cable entering from the top (see README); check the insertion side on the drawing
J2,1,Camera/power connector SH 1.0 mm 3 P right angle,SMD P=1mm,C3029342,WAFER-SH1.0-3PWB,extended,0.0925,yes,Same type as the COOAI board; solder pads in parallel
C3-C14,12,100 nF X7R,0402,C1525,CL05B104KO5NNNC,basic,0.0024,yes,8 decoder pins + RSTB + 2 video coupling + mic
C15-C24,10,1 uF X5R,0402,C52923,CL05A105KA5NQNC,basic,0.0057,yes,Analog rails + LDO in/out + 2 mic coupling
C25-C27,3,10 uF X5R,0603,C19702,CL10A106KP8NNNC,basic,0.0233,yes,DVDD bulk + buck in/out
C28-C30,3,22 uF X5R 25 V,0805,C45783,CL21A226MAQNNNE,basic,0.1084,yes,5 V input + camera out + buck out
R4-R5,2,10 k 1%,0402,C25744,0402WGF1002TCE,basic,0.001,yes,RSTB pull-up + Q1 gate
R9-R14,6,0 ohm jumpers,0402,C17168,0402WGF0000TCE,basic,0.0012,3 of 6,Fitted: R9 VIO from U4 + R13/R14 mic series. Not fitted: R10 VIO from 3.3 V / R11 MCLK-XTI / R12 FPC 3V3
R15,1,Mic attenuator across the pair (value TBD),0402,C25744,0402WGF1002TCE,basic,0.001,no,Placeholder 10 k; value from the breadboard test
